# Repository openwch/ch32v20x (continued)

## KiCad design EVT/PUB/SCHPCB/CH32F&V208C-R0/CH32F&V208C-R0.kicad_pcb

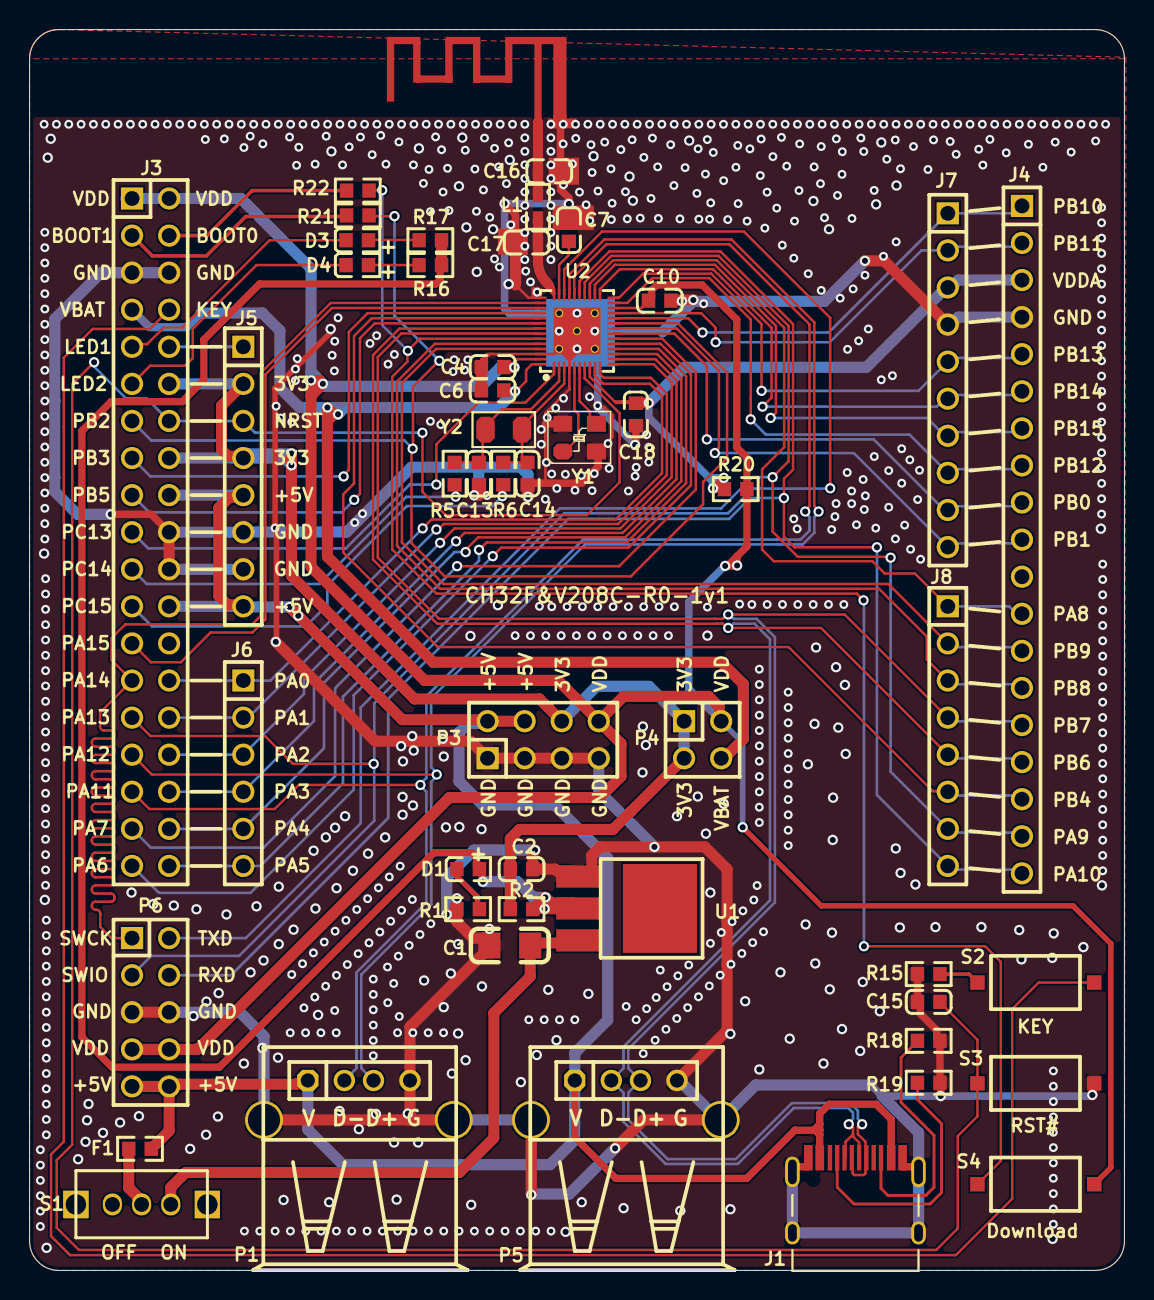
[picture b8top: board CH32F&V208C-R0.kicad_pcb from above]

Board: 2 copper layers, 75.0 x 85.0 mm, 50 parts (0 on the bottom side), 65 nets.

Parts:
C1: 10uF; 3216_C
C2: 10uF; 0603_C
C4, C6, C10, C15, C18: 0.1uF; 0603_C
C7: 1uF; 0603_C
C13, C14: 12pF; 0603_C
C16, C17: 1.8pF; 0603_C
D1: power; 0603+
D3, D4: RED; 0603+
E1: ANTENNA; ANT-F-1-2.4G-1.6mmFR4
F1: 500mA; 0603
J1: TYPE-C-Receptacle-2.0
J3: HEADER 19x2; IDC38-2.54MM
J4: Header 19; SIP19-2.54mm
J5, J8: Header 8; SIP8-2.54mm
J6: Header 6; SIP6-2.54MM
J7: Header 10; SIP10-2.54mm
L1: 1.8nH; 0603
P1, P5: USB; USBAF
P3: HEADER 4x2; IDC8-2.54mm
P4: Header 2X2; IDC4-2.54mm
P6: LINK; IDC10-2.54mm
R1, R16, R17: 1K; 0603
R2, R20: 0Ω; 0603
R5, R6: NC(0R); 0603
R15, R21, R22: 10K; 0603
R18, R19: NC(5.1K); 0603
S1: SW SPDT; SW1
S2: KEY; SMD_6.1x3.65x2.5mm-KEY
S3: RST#; SMD_6.1x3.65x2.5mm-KEY
S4: Download; SMD_6.1x3.65x2.5mm-KEY
U1: 1117-3.3V; SOT-223
U2: CH32V208C; QFN48_5x5
Y1: 32MHz; XT3225
Y2: 32768Hz; FC-135

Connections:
3V3: C2.1, J3.12, J3.16, J5.2, J5.4, P3.6, P4.1, P4.3, R2.1
3V3S: D1.1, R2.2, R16.1, R17.1, U1.2
+5V: F1.1, J1.A4, J1.B4, J3.18, J3.24, J5.5, J5.8, P1.1, P3.2, P3.4, P5.1, P6.9, P6.10
ANT: C17.2, L1.1, U2.34
BOOT0: R22.2, S4.2, U2.43
BOOT1: J3.13, R21.1, U2.19
CC1: J1.A5, R19.1
CC2: J1.B5, R18.1
GND: C1.2, C2.2, C4.2, C6.2, C7.2, C10.1, C13.1, C14.1, C15.1, C16.1, C17.1, C18.2, E1.0, J1.0, J1.A1, J1.B1, J3.5, J3.6, J3.20, J3.22, J4.4, J5.6, J5.7, J7.4, P1.0, P1.4, P3.1, P3.3, P3.5, P3.7, P5.0, P5.4, P6.5, P6.6, R1.1, R15.1, R18.2, R19.2, S3.1, U1.1, U2.0, U2.4, U2.35, U2.46, Y1.2, Y1.4
KEY: J3.8, S2.1
LED1: D3.2, J3.9
LED2: D4.2, J3.11
NRST: C15.2, J3.14, J5.3, S3.2, U2.7
NetC16_2: C16.2, E1.1, L1.2
NetD1_2: D1.2, R1.2
NetD3_1: D3.1, R17.2
NetD4_1: D4.1, R16.2
NetF1_2: F1.2, S1.1
NetJ3_3: J3.3, R21.2
NetJ3_4: J3.4, R22.1
NetJ3_10: J3.10, J5.1
NetR15_2: R15.2, S2.2
PA0: J3.28, J6.1, U2.9
PA1: J3.30, J6.2, U2.10
PA2: J3.32, J6.3, U2.11
PA3: J3.34, J6.4, U2.12
PA4: J3.36, J6.5, U2.13
PA5: J3.38, J6.6, U2.14
PA6: J3.37, U2.15
PA7: J3.35, U2.16
PA8: J4.12, J8.1, U2.27
PA9: J4.18, J8.7, P6.2, U2.28
PA10: J4.19, J8.8, P6.4, U2.29
PA11: J3.33, P1.2, U2.30
PA12: J3.31, P1.3, U2.31
PA13: J3.29, P6.3, U2.32
PA14: J3.27, P6.1, U2.36
PA15: J3.25, U2.37
PB0: J4.9, J7.9, U2.17
PB1: J4.10, J7.10, U2.18
PB3: J3.15, U2.38
PB4: J4.17, J8.6, U2.39
PB5: J3.17, U2.40
PB6: J1.A7, J1.B7, J4.16, J8.5, P5.2, U2.41
PB7: J1.A6, J1.B6, J4.15, J8.4, P5.3, U2.42
PB8: J4.14, J8.3, U2.44
PB9: J4.13, J8.2, U2.45
PB10: J4.1, J7.1, U2.20
PB11: J4.2, J7.2, U2.21
PB12: J4.8, J7.8, U2.23
PB13: J4.5, J7.5, U2.24
PB14: J4.6, J7.6, U2.25
PB15: J4.7, J7.7, U2.26
PC13: J3.19, U2.1
PC14: J3.21, R5.1
PC15: J3.23, R6.1
V5V: C1.1, S1.2, U1.3
VBAT: C6.1, J3.7, P4.4, U2.48
VDD: C4.1, C10.2, J3.1, J3.2, P3.8, P4.2, P6.7, P6.8, R20.1, S4.1, U2.22, U2.47
VDDA: C18.1, J4.3, J7.3, R20.2, U2.8
VINTA: C7.1, U2.33
X32IN: C13.2, R5.2, U2.2, Y2.1
X32OUT: C14.2, R6.2, U2.3, Y2.2
XIN: U2.5, Y1.1
XOUT: U2.6, Y1.3

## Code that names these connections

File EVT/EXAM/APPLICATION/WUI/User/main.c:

/*********************************************************************
 * File Name          : main.c
 * Author             : WCH
 * Version            : V1.0.0
 * Date               : 2026/08/06
 * Description        : Main program body.
 *********************************************************************************
* Copyright (c) 2023 Nanjing Qinheng Microelectronics Co., Ltd.
* Attention: This software (modified or not) and binary are used for 
* microcontroller manufactured by Nanjing Qinheng Microelectronics.
*******************************************************************************/

/*
 *@Note
 A demo for wui
  pins: 
    FLASH_CS   -- PA4
    FLASH_DO   -- PA6
    FLASH_DI   -- PA7
    FLASH_CLK  -- PA5
    
    LCD_LED    -- PB9
    LCD_DC     -- PB10
    LCD_RST    -- PB11
    LCD_CS     -- PB12
    LCD_SCK    -- PB13
    LCD_MOSI   -- PB15


 */


#include <math.h>
#include "debug.h"
#include "string.h"
#include "lcd.h"
#include "flash.h"
#include "config.h"
#include "wui.h"
#include "wui_port.h"
#include "wui_user/wui_page.h"

/* Global define */

/* Global Variable */


#define TIM_PCK (8000ul)

/*********************************************************************
 * @fn      TIM4_init
 *
 * @brief   Initialize TIM2 for WCHGUI
 *        
 * @return  none.
 */
void TIM4_init()
{
    RCC_APB1PeriphClockCmd(RCC_APB1Periph_TIM4, ENABLE);

    TIM_TimeBaseInitTypeDef TIM_TimeBaseInitStructure = {0};

    TIM_Cmd(TIM4, DISABLE);

    TIM_TimeBaseInitStructure.TIM_Period        = 0xffff;
    TIM_TimeBaseInitStructure.TIM_Prescaler     = ((SystemCoreClock) / TIM_PCK) - 1;
    TIM_TimeBaseInitStructure.TIM_ClockDivision = TIM_CKD_DIV1;
    TIM_TimeBaseInitStructure.TIM_CounterMode   = TIM_CounterMode_Up;
    TIM_TimeBaseInit(TIM4, &TIM_TimeBaseInitStructure);

    TIM_ARRPreloadConfig(TIM4, DISABLE);
    TIM_ClearFlag(TIM4, TIM_FLAG_Update);

    TIM_Cmd(TIM4, ENABLE);
}

/*********************************************************************
 * @fn      TIM3_Encoder_Init
 *
 * @brief   Initialize TIM1 for encoder
 *        
 * @return  none.
 */
void TIM3_Encoder_Init()
{
    TIM_TimeBaseInitTypeDef TIM_TimeBaseStructure;
    TIM_ICInitTypeDef       TIM_ICInitStructure;
    GPIO_InitTypeDef        GPIO_InitStructure = {0};

    RCC_APB2PeriphClockCmd(RCC_APB2Periph_GPIOA, ENABLE);
    RCC_APB1PeriphClockCmd(RCC_APB1Periph_TIM3, ENABLE);
    RCC_APB2PeriphClockCmd(RCC_APB2Periph_AFIO, ENABLE);
    RCC_APB2PeriphClockCmd(RCC_APB2Periph_GPIOB, ENABLE);

    {
        GPIO_PinRemapConfig(GPIO_PartialRemap_TIM3, ENABLE);
        GPIO_InitStructure.GPIO_Pin  = GPIO_Pin_4 | GPIO_Pin_5;
        GPIO_InitStructure.GPIO_Mode = GPIO_Mode_IN_FLOATING;
        GPIO_Init(GPIOB, &GPIO_InitStructure);
    }

    TIM_TimeBaseStructInit(&TIM_TimeBaseStructure);
    TIM_TimeBaseStructure.TIM_Prescaler     = 0x0;
    TIM_TimeBaseStructure.TIM_Period        = 160;
    TIM_TimeBaseStructure.TIM_ClockDivision = TIM_CKD_DIV1;
    TIM_TimeBaseStructure.TIM_CounterMode   = TIM_CounterMode_Up;
    TIM_TimeBaseInit(TIM3, &TIM_TimeBaseStructure);

    TIM_EncoderInterfaceConfig(TIM3, TIM_EncoderMode_TI12, TIM_ICPolarity_Rising, TIM_ICPolarity_Rising);

    TIM_ICStructInit(&TIM_ICInitStructure);
    TIM_ICInitStructure.TIM_ICFilter = 10;
    TIM_ICInit(TIM3, &TIM_ICInitStructure);

    TIM_SetCounter(TIM3, 0);
    TIM_Cmd(TIM3, ENABLE);
}

/*********************************************************************
 * @fn      check_direction
 *
 * @brief    Compute the absolute value of a signed 32-bit integer.
 *        
 * @param   a Signed 32-bit integer.
 *
 * @return  Absolute value of a 
 */
uint32_t static inline iabs(int32_t a)
{
    if (a < 0)
    {
        return -a;
    }
    return a;
}

/*********************************************************************
 * @fn      check_direction
 *
 * @brief   Detect the rotation direction of the encoder
 *        
 * @param   current_value The current count value
 *
 * @return  direction The direction of the encoder's rotation
 */
int32_t check_direction(int current_value)
{

    static int last_value = 0;

    if (current_value == last_value)
    {
        return 0;
    }

    int diff = current_value - last_value;
    if (iabs(diff) < 4)
    {
        return 0;
    }

    int32_t direction;

    if (iabs(diff) < 80)
    {
        if (diff > 0)
        {
            direction = 1;
        }
        else
        {
            direction = -1;
        }
    }
    else
    {
        if (diff > 0)
        {
            direction = -1;
        }
        else
        {
            direction = 1;
        }
    }

    last_value = current_value;
    return direction;
}

#define ENC_KEY_PORT GPIOA
#define ENC_KEY_PIN  (GPIO_Pin_15)

#define ENC_KEY()    ((ENC_KEY_PORT->INDR & ENC_KEY_PIN) == 0)

uint32_t key3_state = 0;
/*********************************************************************
 * @fn      Key_GPIOInit
 *
 * @brief   Initialization of the key pins of the encoder
 *        
 * @return  none.
 */
void Key_GPIOInit(void)
{

    GPIO_InitTypeDef GPIO_InitStructure = {0};

    GPIO_InitStructure.GPIO_Pin  = ENC_KEY_PIN;
    GPIO_InitStructure.GPIO_Mode = GPIO_Mode_IPU;
    GPIO_Init(ENC_KEY_PORT, &GPIO_InitStructure);
}

static uint8_t wui_heap_buffer[4 * 1024];

/*********************************************************************
 * @fn      main
 *
 * @brief   Main program.
 *
 * @return  none
 */
int main(void)
{

    SystemCoreClockUpdate();
    Delay_Init();
    USART_Printf_Init(115200);
    printf("SystemClk:%d\r\n", SystemCoreClock);
    printf(__TIME__ "\n");

    SPI_FLASH_Init();

    uint32_t id = SPI_Flash_ReadJedecDeviceID();
    printf("flash_id %x\n", id);

    LCD_Init();

    TIM3_Encoder_Init();
    TIM4_init();
    Key_GPIOInit();

    wui_init_data_t data = {
        .page_count = WUI_PAGE_COUNT,
        .width      = LCD_WIDTH,
        .height     = LCD_HEIGHT,
        .heap_addr  = wui_heap_buffer,
        .heap_size  = sizeof(wui_heap_buffer),
    };

    wui_init(&data);

    wui_register_hal(wui_get_hal());

    wui_page_switch(WUI_START_PAGE);

    while (1)
    {

        uint16_t now = TIM4->CNT;
        if (now > 16)
        {
            now       = now / 8;
            TIM4->CNT = 0;

            wui_page_ui_tick(now);
        }

        wui_page_ui_update();
        uint32_t tcnt = TIM3->CNT;

        int32_t dir = check_direction(tcnt);

        if (dir > 0)
        {
            HW_Key_event('a');
        }
        else if (dir < 0)
        {
            HW_Key_event('d');
        }

        uint32_t k3 = ENC_KEY();
        if (k3)
        {
            if (key3_state)
            {
            }
            else
            {
                key3_state = 1;
                HW_Key_event('b');
            }
        }
        else
        {
            key3_state = 0;
        }
    }

    while (1)
    {
    }
}

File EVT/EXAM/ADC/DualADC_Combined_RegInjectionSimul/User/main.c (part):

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/*
 *@Note
 *dual ADC combined regular + injection + simultaneous sampling routine:
 *Rule group ADC1 channel 1 (PA1), ADC2 channel 4 (PA4), injection group ADC1
 *channel 3 (PA3) ADC2 channel 5 (PA5))
 *The rule group injection groups are all triggered by software, and the dual ADC
 *rule group data is obtained through the DMA interrupt, and the dual ADC injection
 *group data is obtained through the ADC interrupt.
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
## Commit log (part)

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2023-02-01 first submission
2023-12-01 V1.9
2024-02-26 V2.0
2024-05-09 v2.1
2024-06-14 fix warning -Wstrict-prototypes
2024-11-11 V2.2
2026-01-07 V2.31
